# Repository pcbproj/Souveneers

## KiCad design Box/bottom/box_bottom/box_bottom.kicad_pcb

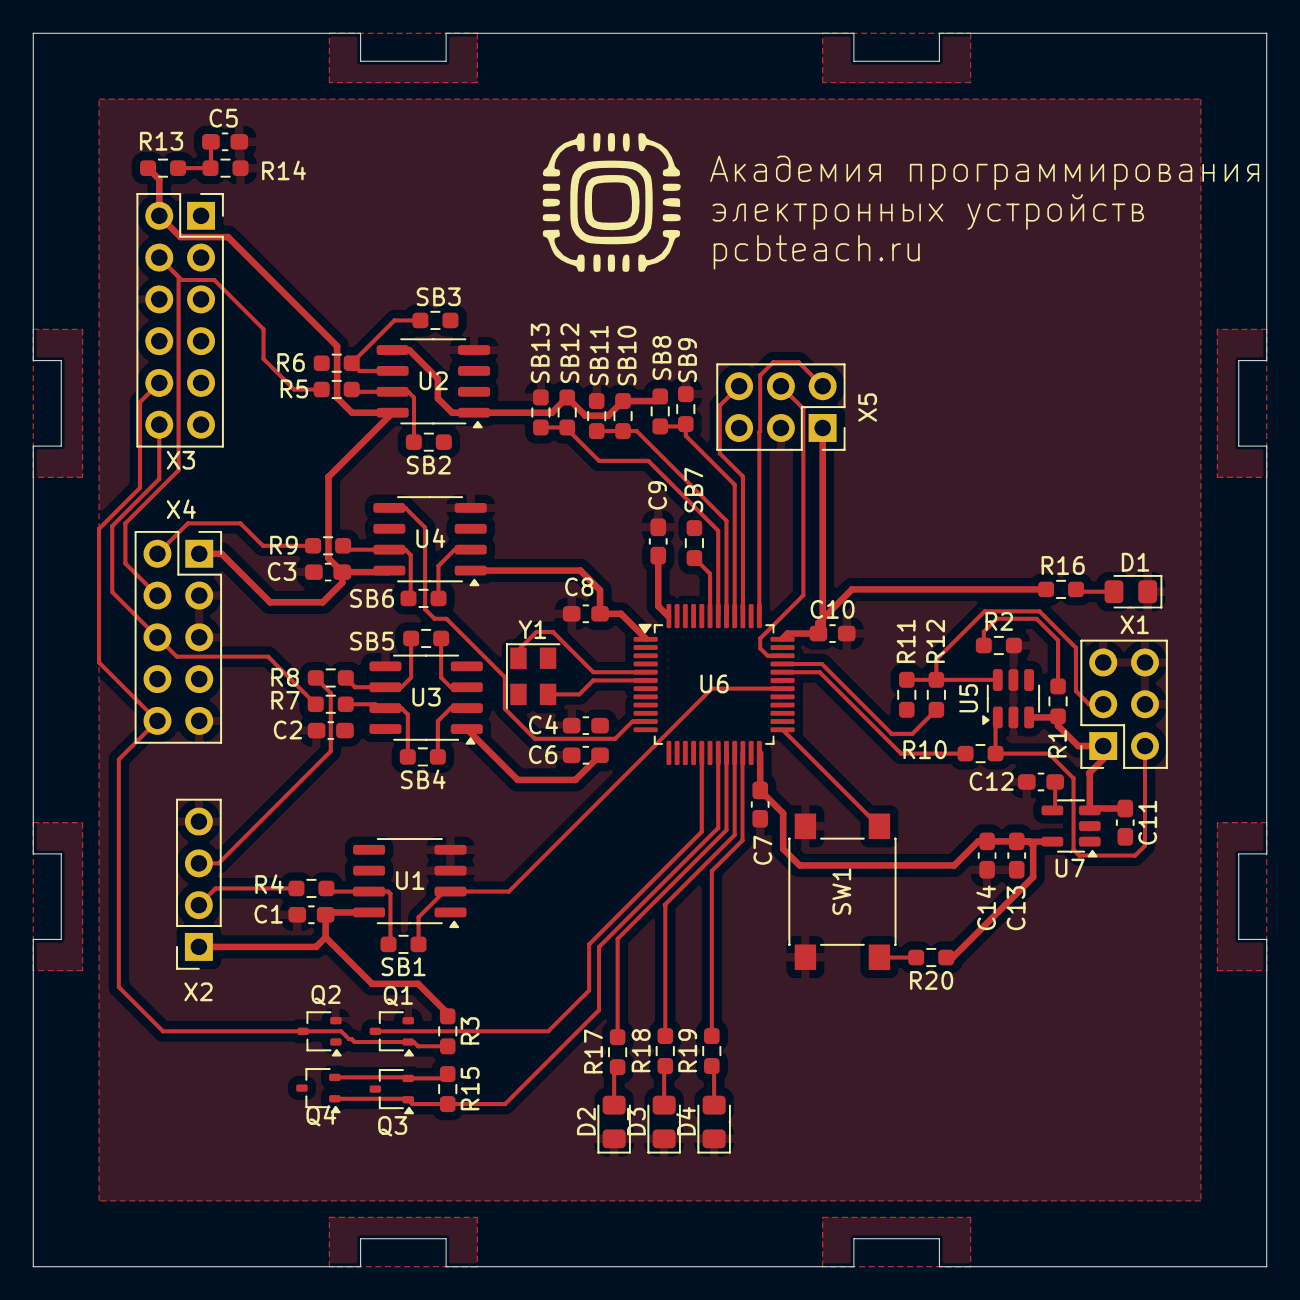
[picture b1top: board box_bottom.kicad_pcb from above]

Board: 2 copper layers, 75.0 x 75.0 mm, 69 parts (0 on the bottom side), 54 nets.

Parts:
C1, C2, C3, C4, C6, C7, C8, C9, C10, C14: 100n; C_0603_1608Metric_Pad1.08x0.95mm_HandSolder
C5: 1n; C_0603_1608Metric_Pad1.08x0.95mm_HandSolder
C11, C13: 1u; C_0603_1608Metric_Pad1.08x0.95mm_HandSolder
C12: 10n; C_0603_1608Metric_Pad1.08x0.95mm_HandSolder
D1, D2, D3, D4: LED; LED_0805_2012Metric_Pad1.15x1.40mm_HandSolder
Q1, Q2: 1N7002; SOT-323_SC-70
Q3, Q4: NTS4173; SOT-323_SC-70
R1, R13: 4k7; R_0603_1608Metric_Pad0.98x0.95mm_HandSolder
R2, R3, R14, R15, R20: 10k; R_0603_1608Metric_Pad0.98x0.95mm_HandSolder
R4, R5, R6, R7, R8, R9: 100; R_0603_1608Metric_Pad0.98x0.95mm_HandSolder
R10, R12: 22; R_0603_1608Metric_Pad0.98x0.95mm_HandSolder
R11: 1k5; R_0603_1608Metric_Pad0.98x0.95mm_HandSolder
R16: 330; R_0603_1608Metric_Pad0.98x0.95mm_HandSolder
R17, R18, R19: 470; R_0603_1608Metric_Pad0.98x0.95mm_HandSolder
SB1, SB2, SB3, SB4, SB5, SB6, SB7, SB8, SB9, SB10, SB11, SB12, SB13: JUMPER; R_0603_1608Metric_Pad0.98x0.95mm_HandSolder
SW1: BUTTON1; SW_SPST_PTS645
U1, U2, U3, U4: SN74LVC2T45; SOIC-8_3.9x4.9mm_P1.27mm
U5: ESDA5V3SC6; SOT-23-6
U6: STM32F103CBT6; LQFP-48_7x7mm_P0.5mm
U7: LP2985N; SOT-23-5
X1: Conn_01x06_Socket; PinSocket_2x03_P2.54mm_Vertical
X2: CONN-04P1L; PinSocket_1x04_P2.54mm_Vertical
X3: CONN-12P2L; PinSocket_2x06_P2.54mm_Vertical
X4: CONN-10P2L; PinSocket_2x05_P2.54mm_Vertical
X5: CONN-06P1L; PinSocket_2x03_P2.54mm_Vertical
Y1: 8MHz; Crystal_SMD_EuroQuartz_MT-4Pin_3.2x2.5mm

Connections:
+3V3BM: C6.1 (C1), C7.1 (C1), C8.1 (C1), C9.1 (C1), C10.1 (C1), C13.1 (C1), C14.1 (C1), Q3.3 (D), R16.2 (R2), R20.1 (R1), SB8.1 (J1), SB10.1 (J1), SB12.1 (J1), U1.1 (VCCA), U1.5 (DIR), U2.1 (VCCA), U2.5 (DIR), U3.1 (VCCA), U4.1 (VCCA), U6.1 (VBAT), U6.9 (VDDA), U6.24 (VDD), U6.36 (VDD), U6.48 (VDD), U7.5 (VO), X5.1
/5VUSB: C11.1 (C1), R1.1 (R1), U5.3 (IO2), U7.1 (VIN), U7.3 (ENA), X1.1
/BMBTN: R20.2 (R2), SW1.1 (CMN), U6.25 (PB12)
/JRST: C4.1 (C1), U6.7 (nRST), X5.5
/JSWCLK: U6.37 (PA14/SWCLK), X5.2
/JSWDIO: U6.34 (PA13/SWDIO), X5.4
/JSWO: U6.39 (JTDO/PB3), X5.6
/LED0: R17.2 (R2), U6.20 (PB2)
/LED1: R18.2 (R2), U6.21 (PB10)
/LED2: R19.2 (R2), U6.22 (PB11)
/PWR_BR: Q3.1 (G), Q4.1 (G), R15.1 (R1), U6.19 (PB1)
/TPWR: C5.1 (C1), R13.2 (R2), R14.1 (R1), U6.18 (PB0)
/UD+: R12.1 (R1), U6.33 (PA12)
/UD-: R10.2 (R2), U6.32 (PA11)
/VBUS: R1.2 (R2), R2.1 (R1), U6.26 (PB13)
/iRST: Q2.1 (G), U6.12 (PA2)
/iRST_SENSE: Q1.3 (D), U6.17 (PA7)
/iRXD: SB5.1 (J1), U3.3 (A2), U6.31 (PA10)
/iTCK: SB2.1 (J1), U2.2 (A1), U6.15 (PA5)
/iTDI: SB3.1 (J1), U2.3 (A2), U6.13 (PA3)
/iTDO: SB4.1 (J1), SB7.2 (J2), U3.2 (A1), U6.16 (PA6)
/iTMS: SB6.1 (J1), U4.2 (A1), U6.14 (PA4)
/iTMS_DIR: U4.5 (DIR), U6.11 (PA1)
/iTXD: SB1.1 (J1), U1.2 (A1), U6.30 (PA9)
/xPWR: C1.2 (C2), C2.2 (C2), C3.2 (C2), Q4.3 (D), R3.1 (R1), R13.1 (R1), U1.8 (VCCB), U2.8 (VCCB), U3.8 (VCCB), U4.8 (VCCB), X2.1, X3.2, X4.1
/xRST: Q1.1 (G), Q2.3 (D), R3.2 (R2), X3.10, X4.10
/xRXD: R8.1 (R1), X2.3
/xTCK: R5.1 (R1), X3.4, X4.4
/xTDI: R6.1 (R1), X4.8
/xTDO: R7.1 (R1), X3.12, X4.6
/xTMS: R9.1 (R1), X3.8, X4.2
/xTXD: R4.1 (R1), X2.2
unnamed: C12.1 (C1), U7.4 (BYP)
unnamed: D1.2 (A), R16.1 (R1)
unnamed: D2.2 (A), R17.1 (R1)
unnamed: D3.2 (A), R18.1 (R1)
unnamed: D4.2 (A), R19.1 (R1)
unnamed: Q3.2 (S), Q4.2 (S), R15.2 (R2)
unnamed: R4.2 (R2), SB1.2 (J2), U1.7 (B1)
unnamed: R5.2 (R2), SB2.2 (J2), U2.7 (B1)
unnamed: R6.2 (R2), SB3.2 (J2), U2.6 (B2)
unnamed: R7.2 (R2), SB4.2 (J2), U3.7 (B1)
unnamed: R8.2 (R2), SB5.2 (J2), U3.6 (B2)
unnamed: R9.2 (R2), SB6.2 (J2), U4.7 (B1)
unnamed: R10.1 (R1), U5.1 (IO1), X1.2
unnamed: R11.1 (R1), U6.29 (PA8)
unnamed: R11.2 (R2), R12.2 (R2), U5.6 (IO4), X1.3
unnamed: SB7.1 (J1), U6.43 (PB7)
unnamed: SB8.2 (J2), SB9.1 (J1), U6.40 (JRST/PB4)
unnamed: SB10.2 (J2), SB11.1 (J1), U6.41 (PB5)
unnamed: SB12.2 (J2), SB13.1 (J1), U6.42 (PB6)
unnamed: U6.5 (PD0/XI), Y1.1 (Q1)
unnamed: U6.6 (PD1/XO), Y1.3 (Q2)
PGND: C1.1 (C1), C2.1 (C1), C3.1 (C1), C4.2 (C2), C5.2 (C2), C6.2 (C2), C7.2 (C2), C8.2 (C2), C9.2 (C2), C10.2 (C2), C11.2 (C2), C12.2 (C2), C13.2 (C2), C14.2 (C2), D1.1 (K), D2.1 (K), D3.1 (K), D4.1 (K), Q1.2 (S), Q2.2 (S), R2.2 (R2), R14.2 (R2), SB9.2 (J2), SB11.2 (J2), SB13.2 (J2), SW1.2 (NO), U1.3 (A2), U1.4 (GND), U2.4 (GND), U3.4 (GND), U3.5 (DIR), U4.4 (GND), U5.2 (GND), U5.5 (GND), U6.8 (VSSA), U6.23 (VSS), U6.35 (VSS), U6.44 (PH3/BOOT0), U6.47 (VSS), U7.2 (GND), X1.4, X1.5, X1.6, X2.4, X3.5, X3.6, X4.3, X4.5, X4.9, X5.3, Y1.2 (CMN)

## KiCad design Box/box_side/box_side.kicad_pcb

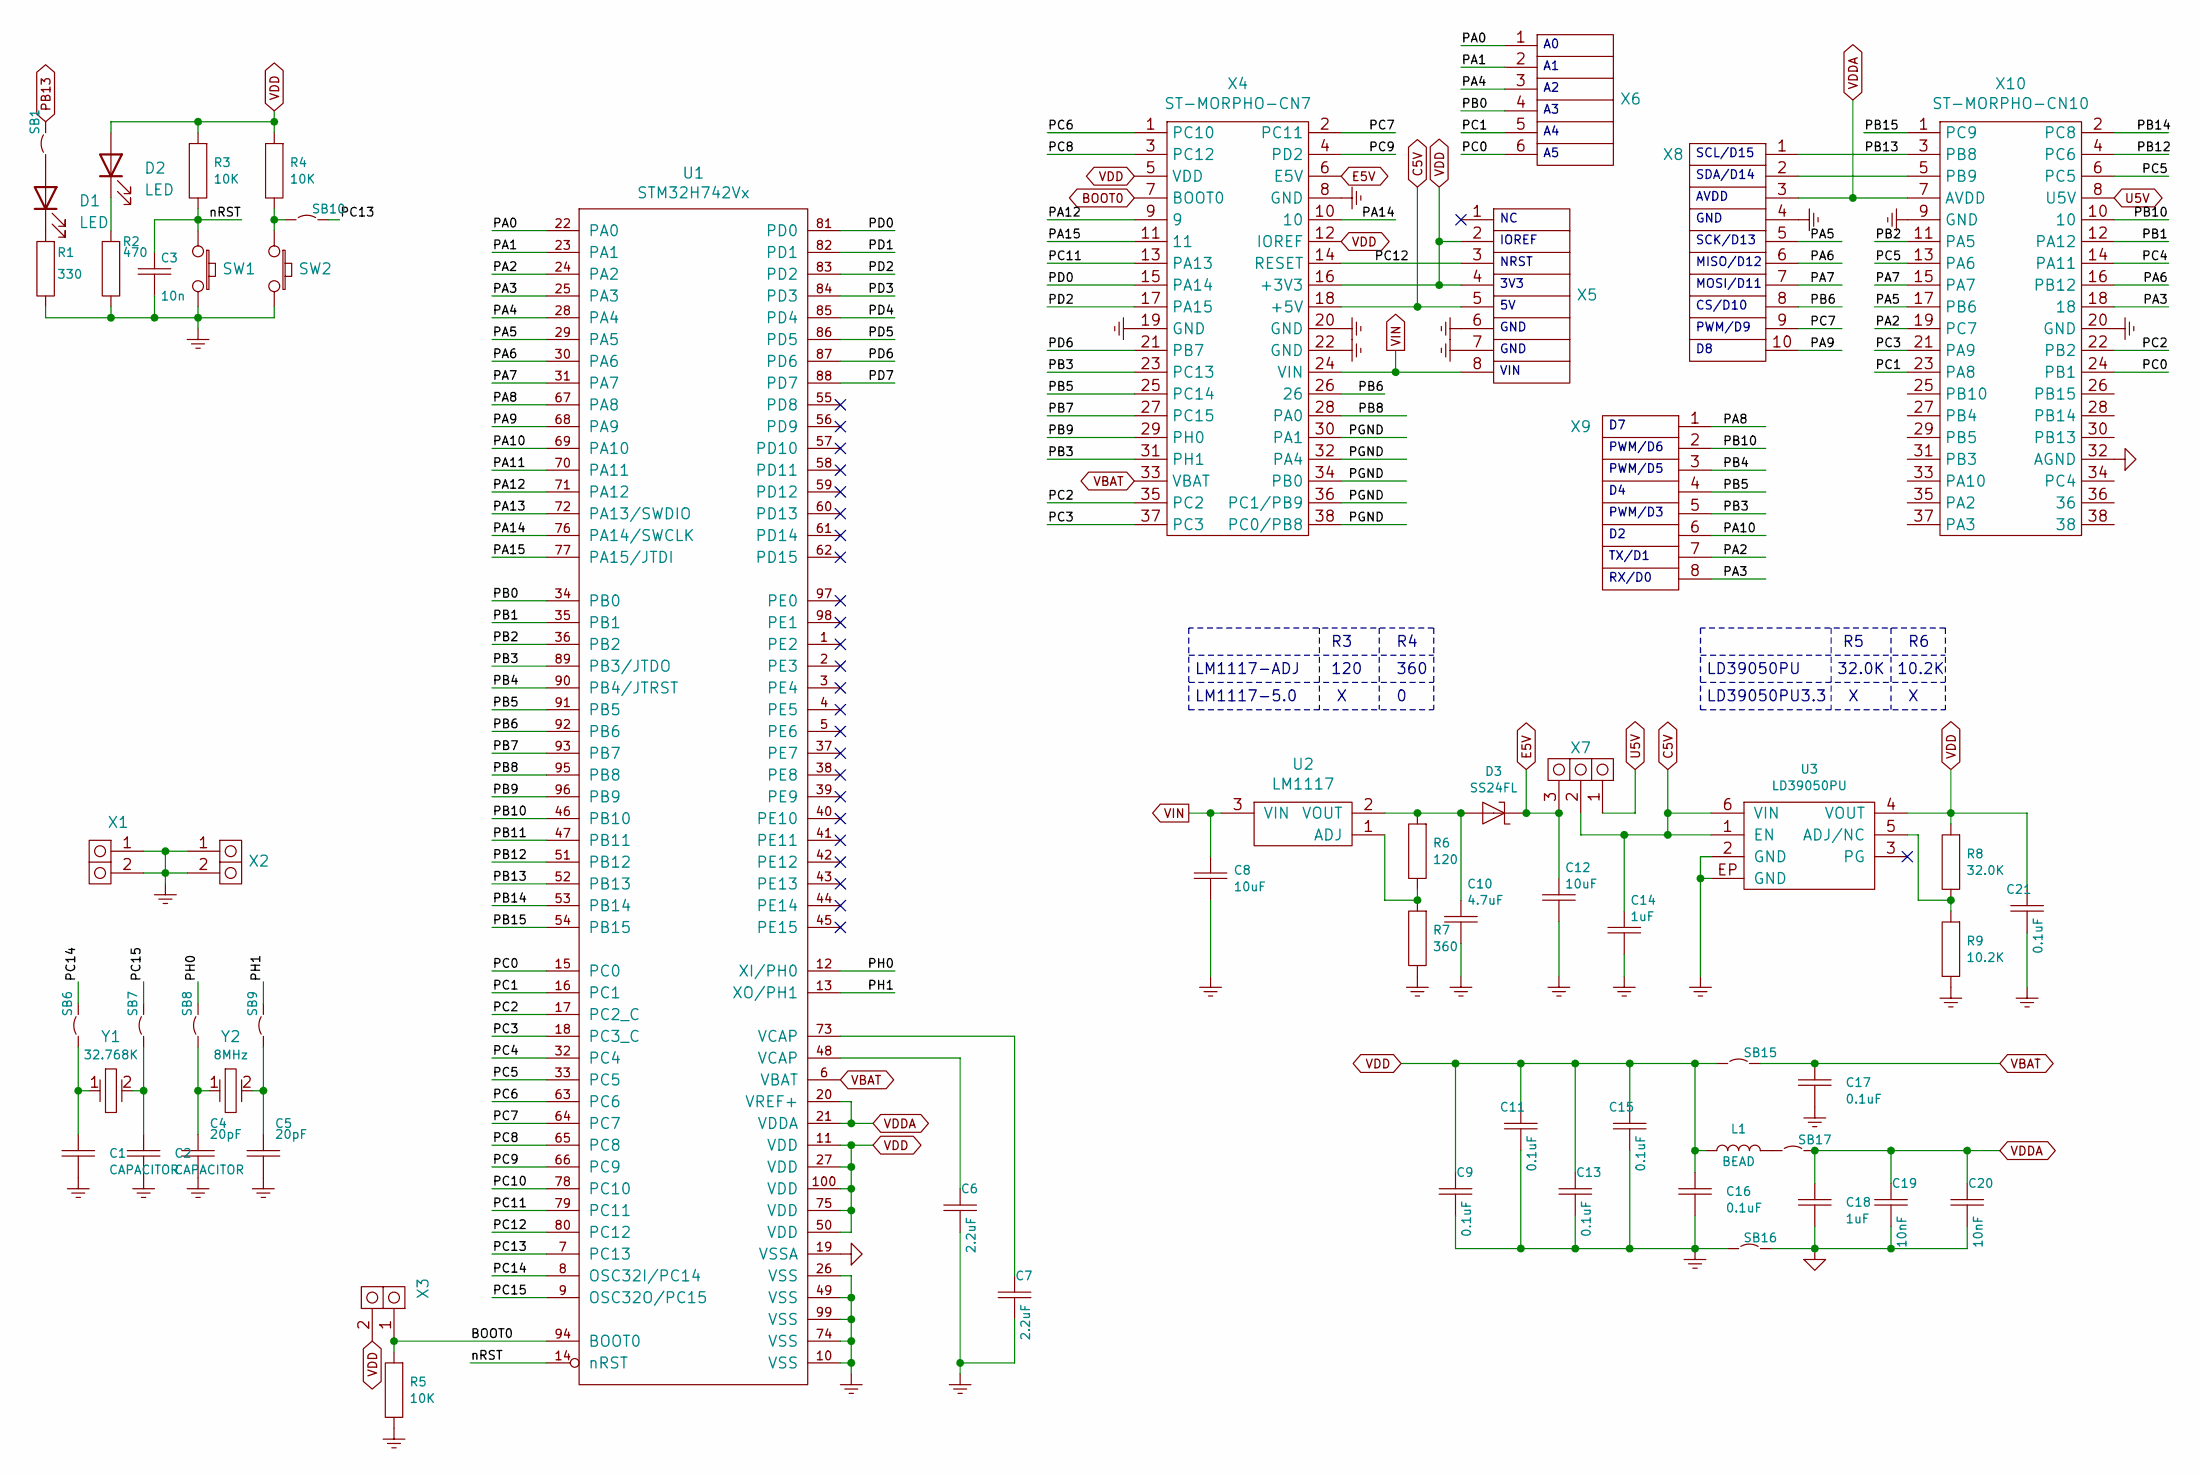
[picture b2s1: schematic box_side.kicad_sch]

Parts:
C1, C2: CAPACITOR; C_0603_1608Metric_Pad1.08x0.95mm_HandSolder
C3: 10n; C_0603_1608Metric_Pad1.08x0.95mm_HandSolder
C4, C5: 20pF; C_0603_1608Metric_Pad1.08x0.95mm_HandSolder
C6, C7: 2.2uF; C_0603_1608Metric_Pad1.08x0.95mm_HandSolder
C8, C12: 10uF; C_0805_2012Metric_Pad1.18x1.45mm_HandSolder
C9, C11, C13, C15, C16, C17, C21: 0.1uF; C_0603_1608Metric_Pad1.08x0.95mm_HandSolder
C10: 4.7uF; C_0603_1608Metric_Pad1.08x0.95mm_HandSolder
C14, C18: 1uF; C_0603_1608Metric_Pad1.08x0.95mm_HandSolder
C19, C20: 10nF; C_0603_1608Metric_Pad1.08x0.95mm_HandSolder
D1, D2: LED; LED_0805_2012Metric_Pad1.15x1.40mm_HandSolder
D3: SS24FL; D_SOD-123F
L1: BEAD; L_0805_2012Metric_Pad1.05x1.20mm_HandSolder
R1: 330; R_0603_1608Metric_Pad0.98x0.95mm_HandSolder
R2: 470; R_0603_1608Metric_Pad0.98x0.95mm_HandSolder
R3, R4, R5: 10K; R_0603_1608Metric_Pad0.98x0.95mm_HandSolder
R6: 120; R_0603_1608Metric_Pad0.98x0.95mm_HandSolder
R7: 360; R_0603_1608Metric_Pad0.98x0.95mm_HandSolder
R8: 32.0K; R_0603_1608Metric_Pad0.98x0.95mm_HandSolder
R9: 10.2K; R_0603_1608Metric_Pad0.98x0.95mm_HandSolder
SB1, SB6, SB7, SB8, SB9, SB10, SB15, SB16, SB17: JUMPER; R_0603_1608Metric_Pad0.98x0.95mm_HandSolder
SW1, SW2: BUTTON1; SW_SPST_PTS645
U1: STM32H742Vx; LQFP-100_14x14mm_P0.5mm
U2: LM1117; SOT-223
U3: LD39050PU; DFN-6-1EP_2x1.8mm_P0.5mm_EP1.2x1.6mm
X1, X2: CONN-02P1LA; PinSocket_1x02_P2.54mm_Vertical
X3: CONN-02P1L; PinSocket_1x02_P2.54mm_Vertical
X4: ST-MORPHO-CN7; PinSocket_2x19_P1.27mm_Vertical_SMD
X5, X9: CONN-08P1L; PinSocket_1x08_P2.54mm_Vertical
X6: CONN-06P1L; PinSocket_1x06_P2.54mm_Vertical
X7: CONN-03P1L; PinSocket_1x03_P2.54mm_Vertical
X8: CONN-10P1L; PinSocket_2x05_P2.54mm_Vertical
X10: ST-MORPHO-CN10; PinSocket_2x19_P1.27mm_Vertical_SMD
Y1: 32.768K; Crystal_SMD_EuroQuartz_EQ161-2Pin_3.2x1.5mm_HandSoldering
Y2: 8MHz; Crystal_SMD_5032-2Pin_5.0x3.2mm

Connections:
/PA0: U1.22 (PA0), X6.1
/PA1: U1.23 (PA1), X6.2
/PA2: U1.24 (PA2), X9.7, X10.19 (PC7)
/PA3: U1.25 (PA3), X9.8, X10.18
/PA4: U1.28 (PA4), X6.3
/PA5: U1.29 (PA5), X8.5, X10.17 (PB6)
/PA6: U1.30 (PA6), X8.6, X10.16 (PB12)
/PA7: U1.31 (PA7), X8.7, X10.15 (PA7)
/PA8: U1.67 (PA8), X9.1
/PA9: U1.68 (PA9), X8.10
/PA10: U1.69 (PA10), X9.6
/PA11: U1.70 (PA11)
/PA12: U1.71 (PA12), X4.9
/PA13: U1.72 (PA13/SWDIO)
/PA14: U1.76 (PA14/SWCLK), X4.10
/PA15: U1.77 (PA15/JTDI), X4.11
/PB0: U1.34 (PB0), X6.4
/PB1: U1.35 (PB1), X10.12 (PA12)
/PB2: U1.36 (PB2), X10.11 (PA5)
/PB3: U1.89 (PB3/JTDO), X4.23 (PC13), X4.31 (PH1), X9.5
/PB4: U1.90 (PB4/JTRST), X9.3
/PB5: U1.91 (PB5), X4.25 (PC14), X9.4
/PB6: U1.92 (PB6), X4.26, X8.8
/PB7: U1.93 (PB7), X4.27 (PC15)
/PB8: U1.95 (PB8), X4.28 (PA0)
/PB9: U1.96 (PB9), X4.29 (PH0)
/PB10: U1.46 (PB10), X9.2, X10.10
/PB11: U1.47 (PB11)
/PB12: U1.51 (PB12), X10.4 (PC6)
/PB14: U1.53 (PB14), X10.2 (PC8)
/PB15: U1.54 (PB15), X10.1 (PC9)
/PC0: U1.15 (PC0), X6.6, X10.24 (PB1)
/PC1: U1.16 (PC1), X6.5, X10.23 (PA8)
/PC2: U1.17 (PC2_C), X4.35 (PC2), X10.22 (PB2)
/PC3: U1.18 (PC3_C), X4.37 (PC3), X10.21 (PA9)
/PC4: U1.32 (PC4), X10.14 (PA11)
/PC5: U1.33 (PC5), X10.6 (PC5), X10.13 (PA6)
/PC6: U1.63 (PC6), X4.1 (PC10)
/PC7: U1.64 (PC7), X4.2 (PC11), X8.9
/PC8: U1.65 (PC8), X4.3 (PC12)
/PC9: U1.66 (PC9), X4.4 (PD2)
/PC10: U1.78 (PC10)
/PC11: U1.79 (PC11), X4.13 (PA13)
/PC12: U1.80 (PC12), X4.14 (RESET), X5.3
/PC13: SB10.2 (J2), U1.7 (PC13)
/PC14: SB6.2 (J2), U1.8 (OSC32I/PC14); also elsewhere on the board
/PC15: SB7.2 (J2), U1.9 (OSC32O/PC15); also elsewhere on the board
/PD0: U1.81 (PD0), X4.15 (PA14)
/PD1: U1.82 (PD1)
/PD2: U1.83 (PD2), X4.17 (PA15)
/PD3: U1.84 (PD3)
/PD4: U1.85 (PD4)
/PD5: U1.86 (PD5)
/PD6: U1.87 (PD6), X4.21 (PB7)
/PD7: U1.88 (PD7)
/PH0: SB8.2 (J2), U1.12 (XI/PH0); also elsewhere on the board
/PH1: SB9.2 (J2), U1.13 (XO/PH1); also elsewhere on the board
/nRST: C3.1 (C1), R3.2 (R2), SW1.1 (CMN), U1.14 (nRST)
AGND: C18.2 (C2), C19.2 (C2), C20.2 (C2), SB16.2 (J2), U1.19 (VSSA), X10.32 (AGND)
BOOT0: R5.1 (R1), U1.94 (BOOT0), X3.1, X4.7 (BOOT0)
C5V: C14.1 (C1), U3.1 (EN), U3.6 (VIN), X4.18 (+5V), X5.5, X7.2
E5V: C12.1 (C1), D3.1 (K), X4.6 (E5V), X7.3
unnamed: C1.1 (C1), SB6.1 (J1), Y1.1 (Q1)
unnamed: C2.1 (C1), SB7.1 (J1), Y1.2 (Q2)
unnamed: C4.1 (C1), SB8.1 (J1), Y2.1 (Q1)
unnamed: C5.1 (C1), SB9.1 (J1), Y2.2 (Q2)
unnamed: C6.1 (C1), U1.48 (VCAP)
unnamed: C7.1 (C1), U1.73 (VCAP)
unnamed: C10.1 (C1), D3.2 (A), R6.1 (R1), U2.2 (VOUT)
unnamed: D1.2 (A), SB1.1 (J1)
unnamed: D1.1 (K), R1.1 (R1)
unnamed: D2.1 (K), R2.1 (R1)
unnamed: L1.2 (R2), SB17.1 (J1)
unnamed: R4.2 (R2), SB10.1 (J1), SW2.1 (CMN)
unnamed: R6.2 (R2), R7.1 (R1), U2.1 (ADJ)
unnamed: R8.2 (R2), R9.1 (R1), U3.5 (ADJ/NC)
unnamed: X8.2, X10.5 (PB9)
PB13: SB1.2 (J2), U1.52 (PB13), X8.1, X10.3 (PB8)
PGND: C1.2 (C2), C2.2 (C2), C3.2 (C2), C4.2 (C2), C5.2 (C2), C6.2 (C2), C7.2 (C2), C8.2 (C2), C9.2 (C2), C10.2 (C2), C11.2 (C2), C12.2 (C2), C13.2 (C2), C14.2 (C2), C15.2 (C2), C16.2 (C2), C17.2 (C2), C21.2 (C2), R1.2 (R2), R2.2 (R2), R5.2 (R2), R7.2 (R2), R9.2 (R2), SB16.1 (J1), SW1.2 (NO), SW2.2 (NO), U1.10 (VSS), U1.26 (VSS), U1.49 (VSS), U1.74 (VSS), U1.99 (VSS), U3.2 (GND), U3.EP (GND), X1.1, X1.2, X2.1, X2.2, X4.8 (GND), X4.19 (GND), X4.20 (GND), X4.22 (GND), X4.30 (PA1), X4.32 (PA4), X4.34 (PB0), X4.36 (PC1/PB9), X4.38 (PC0/PB8), X5.6, X5.7, X8.4, X10.9 (GND), X10.20 (GND)
U5V: X7.1, X10.8 (U5V)
VBAT: C17.1 (C1), SB15.2 (J2), U1.6 (VBAT), X4.33 (VBAT)
VDD: C9.1 (C1), C11.1 (C1), C13.1 (C1), C15.1 (C1), C16.1 (C1), C21.1 (C1), D2.2 (A), L1.1 (R1), R3.1 (R1), R4.1 (R1), R8.1 (R1), SB15.1 (J1), U1.11 (VDD), U1.27 (VDD), U1.50 (VDD), U1.75 (VDD), U1.100 (VDD), U3.4 (VOUT), X3.2, X4.5 (VDD), X4.12 (IOREF), X4.16 (+3V3), X5.2, X5.4
VDDA: C18.1 (C1), C19.1 (C1), C20.1 (C1), SB17.2 (J2), U1.20 (VREF+), U1.21 (VDDA), X8.3, X10.7 (AVDD)
VIN: C8.1 (C1), U2.3 (VIN), X4.24 (VIN), X5.8

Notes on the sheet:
120
10.2K
GND
PWM/D9
RX/D0
SCL/D15
MOSI/D11
3V3
AVDD
PWM/D3
TX/D1
VIN
SCK/D13
32.0K
IOREF
LM1117-ADJ
PWM/D6
LM1117-5.0
LD39050PU3.3
CS/D10
360
NRST
LD39050PU
SDA/D14
PWM/D5
MISO/D12

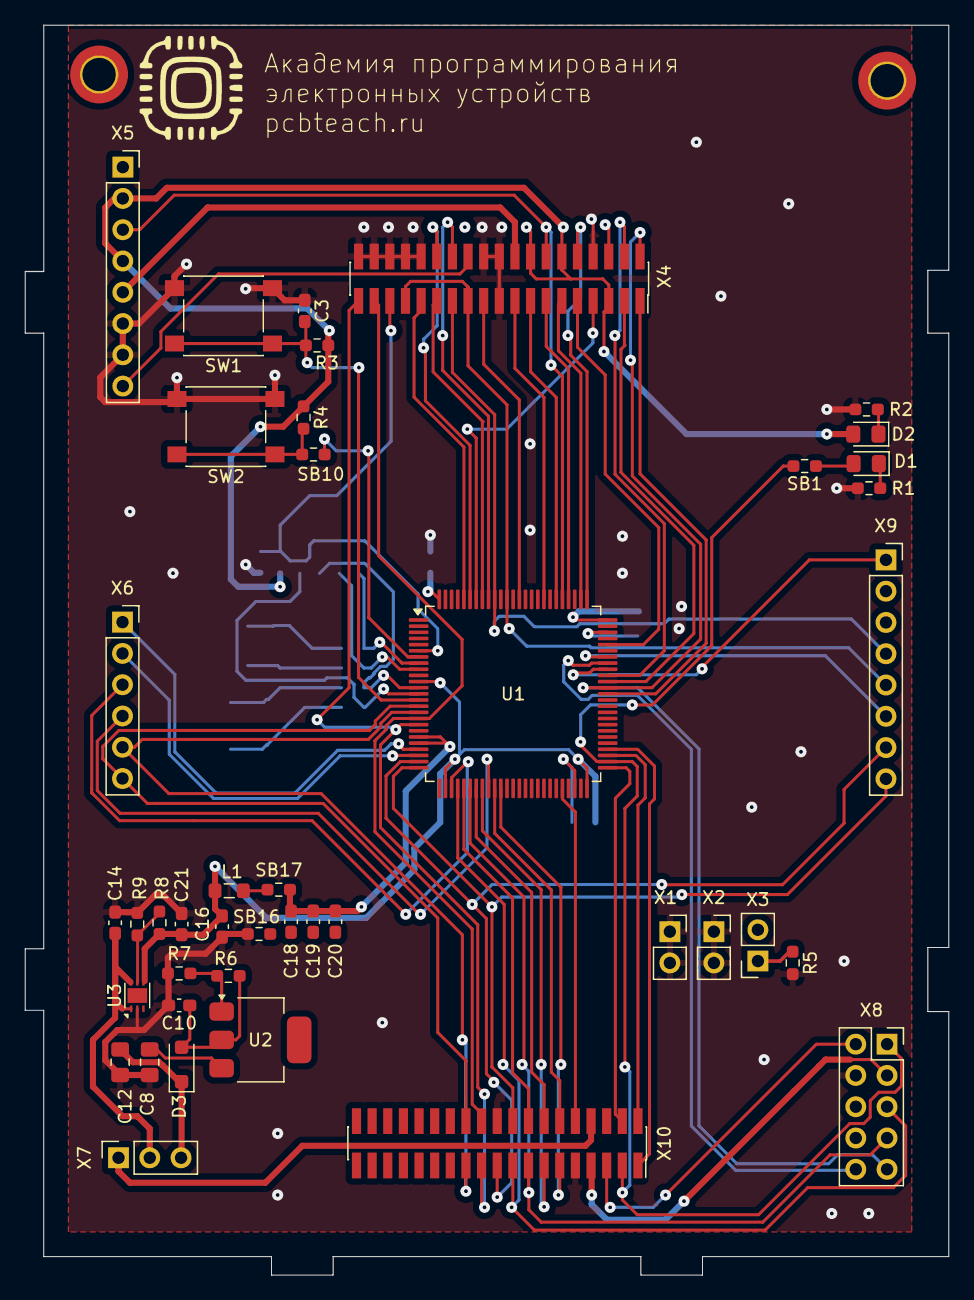
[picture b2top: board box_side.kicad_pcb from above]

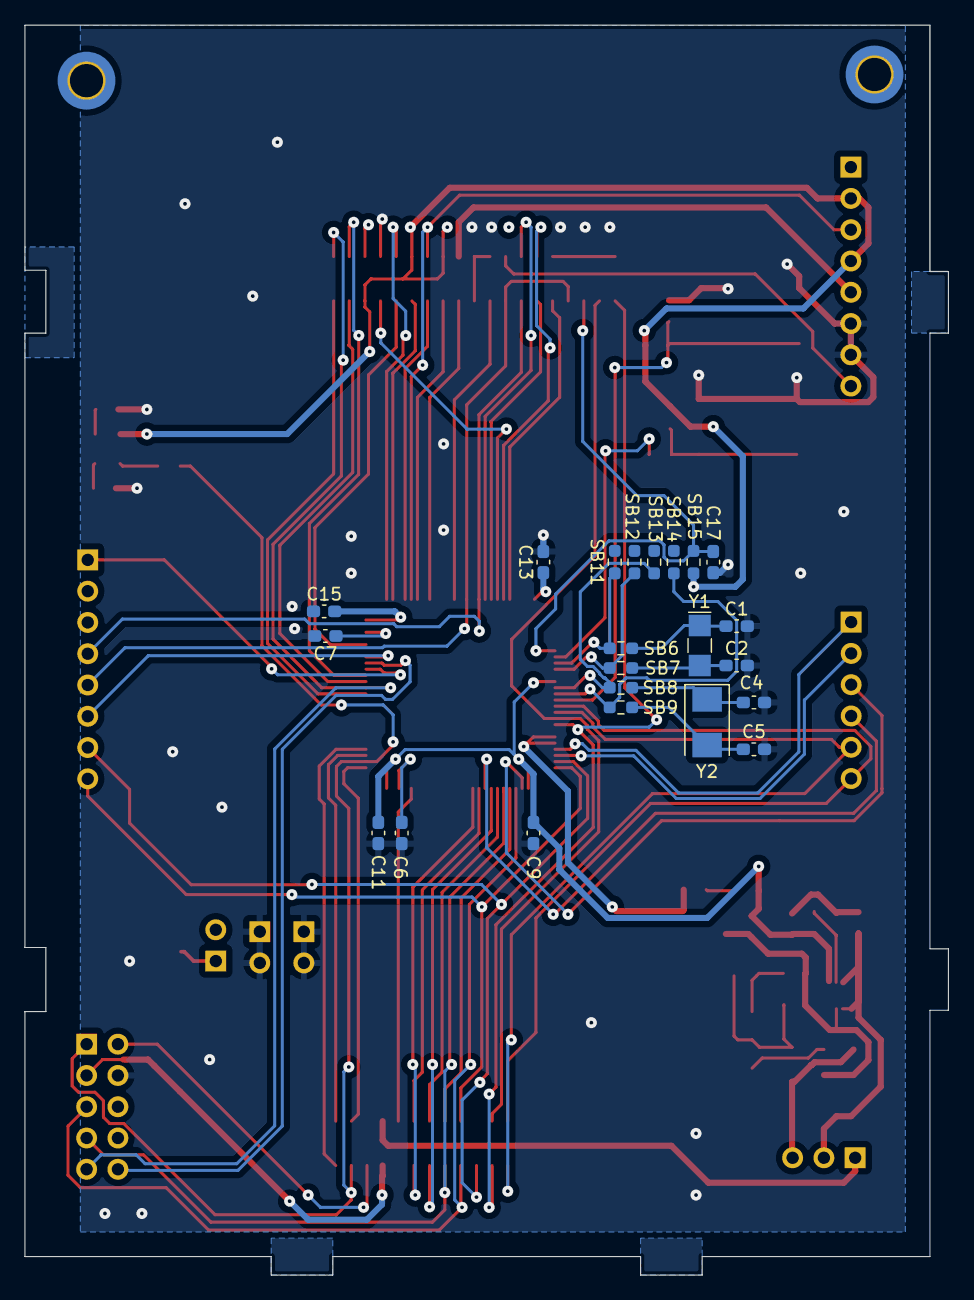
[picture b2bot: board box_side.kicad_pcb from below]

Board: 2 copper layers, 75.0 x 101.5 mm, 64 parts (22 on the bottom side), 75 nets.

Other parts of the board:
SB11, SB12, SB13, SB14: JUMPER; R_0603_1608Metric_Pad0.98x0.95mm_HandSolder

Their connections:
/PC14: SB11.1 (J1); also elsewhere on the board
/PC15: SB12.1 (J1); also elsewhere on the board
/PH0: SB13.1 (J1); also elsewhere on the board
/PH1: SB14.1 (J1); also elsewhere on the board

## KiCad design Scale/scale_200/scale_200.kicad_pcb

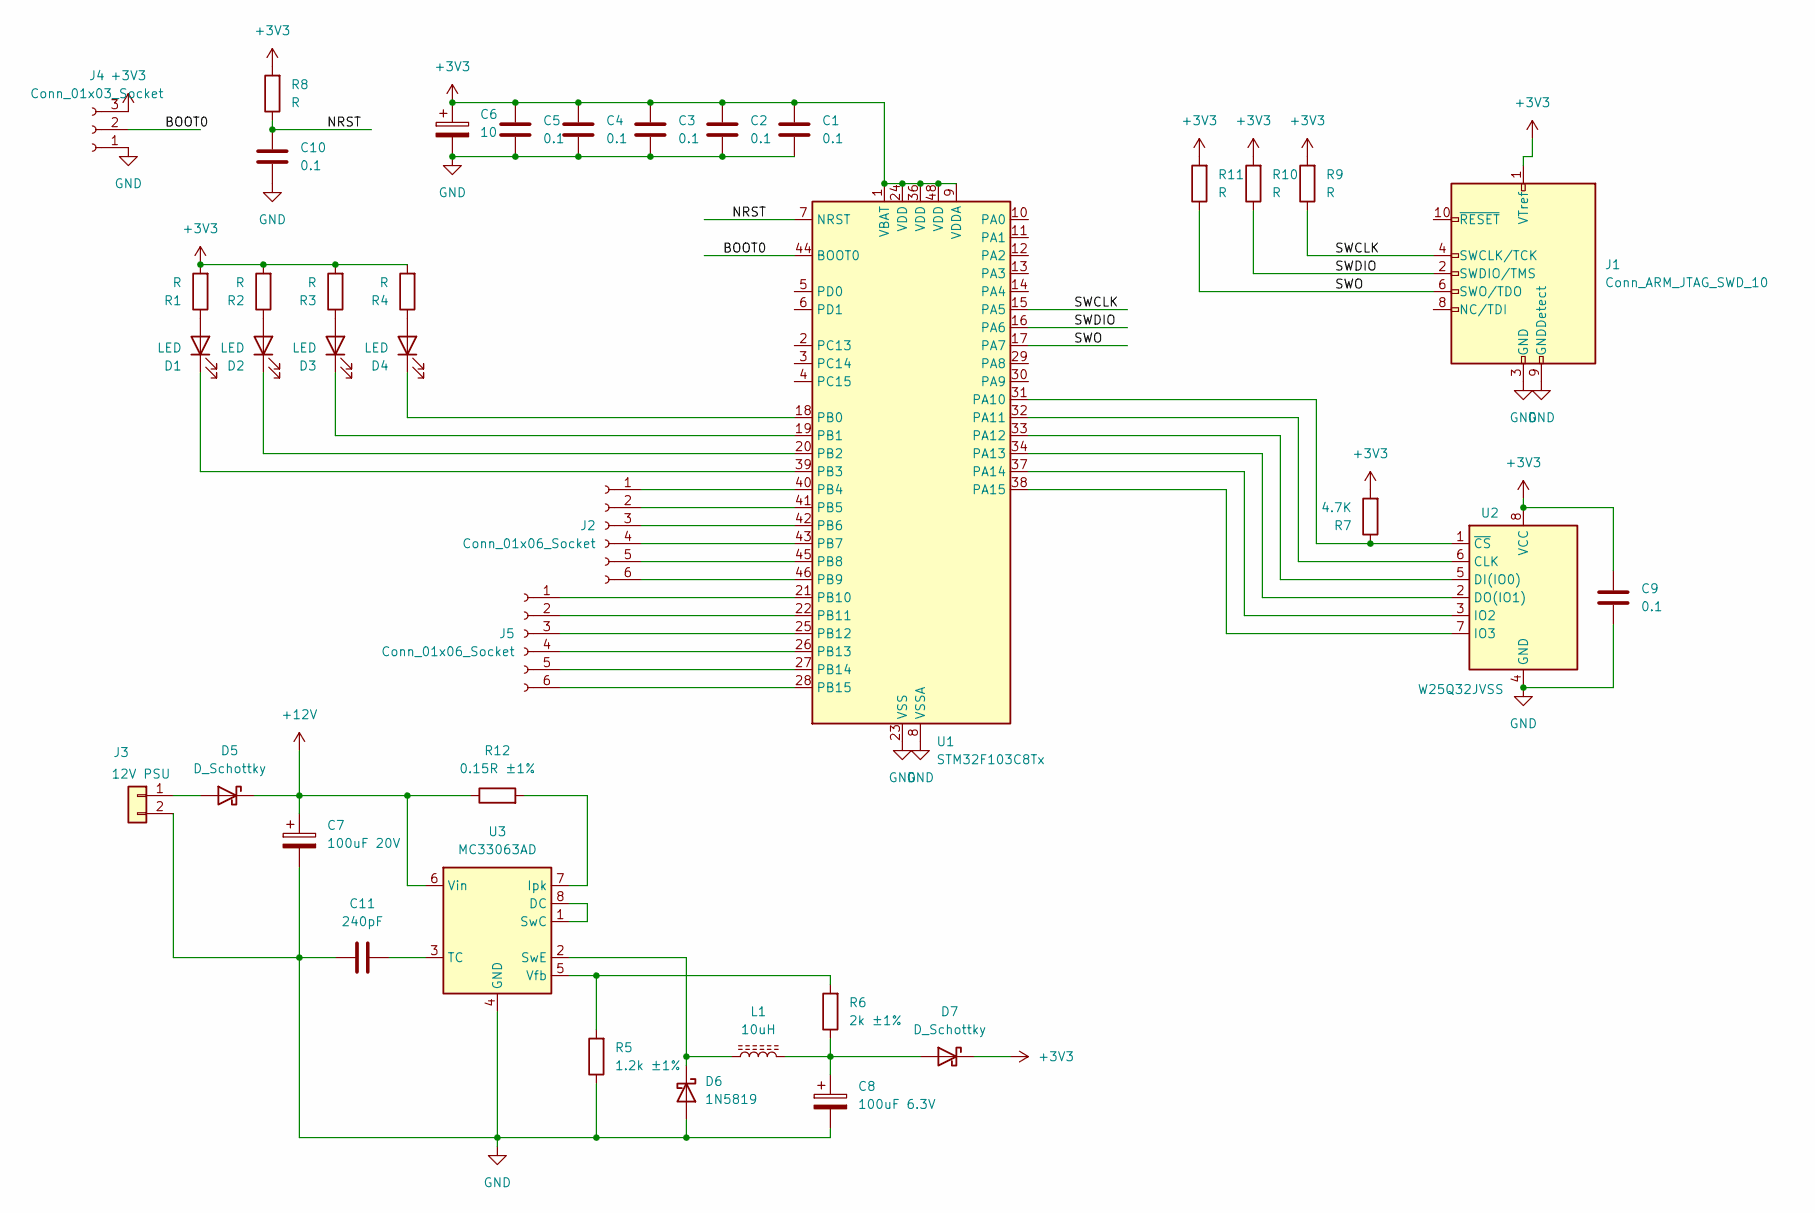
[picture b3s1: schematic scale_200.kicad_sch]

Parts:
C1, C2, C3, C4, C5, C9, C10: 0.1; C_0603_1608Metric
C6: 10; CP_Elec_5x3.9
C7: 100uF 20V; CP_Elec_5x3.9
C8: 100uF 6.3V; CP_Elec_5x3.9
C11: 240pF; C_0603_1608Metric
D1, D2, D3, D4: LED; LED_1206_3216Metric
D5, D7: D_Schottky; D_SOD-123
D6: 1N5819; D_SOD-123
J1: Conn_ARM_JTAG_SWD_10; PinSocket_2x05_P2.54mm_Vertical
J2, J5: Conn_01x06_Socket; PinSocket_1x06_P2.54mm_Vertical
J3: 12V PSU; PinSocket_1x02_P2.54mm_Vertical
J4: Conn_01x03_Socket; PinSocket_1x03_P2.54mm_Vertical
L1: 10uH; L_TDK_SLF6028
R1, R2, R3, R4, R8, R9, R10, R11: R; R_0805_2012Metric_Pad1.20x1.40mm_HandSolder
R5: 1.2k ±1%; R_0805_2012Metric_Pad1.20x1.40mm_HandSolder
R6: 2k ±1%; R_0805_2012Metric_Pad1.20x1.40mm_HandSolder
R7: 4.7K; R_0805_2012Metric_Pad1.20x1.40mm_HandSolder
R12: 0.15R ±1%; R_2512_6332Metric_Pad1.40x3.35mm_HandSolder
U1: STM32F103C8Tx; LQFP-48_7x7mm_P0.5mm
U2: W25Q32JVSS; SOIC-8_5.23x5.23mm_P1.27mm
U3: MC33063AD; SOIC-8_3.9x4.9mm_P1.27mm

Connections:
+3V3: C1.1, C2.1, C3.1, C4.1, C5.1, C6.1, C9.1, D7.1 (K), J1.1 (VTref), J4.3, R1.2, R2.2, R3.2, R4.2, R7.2, R8.2, R9.2, R10.2, R11.2, U1.1 (VBAT), U1.9 (VDDA), U1.24 (VDD), U1.36 (VDD), U1.48 (VDD), U2.8 (VCC)
+12V: C7.1, D5.1 (K), R12.1, U3.6 (Vin)
/BOOT0: J4.2, U1.44 (BOOT0)
/NRST: C10.1, R8.1, U1.7 (NRST)
/SWCLK: J1.4 (SWCLK/TCK), R9.1, U1.15 (PA5)
/SWDIO: J1.2 (SWDIO/TMS), R10.1, U1.16 (PA6)
/SWO: J1.6 (SWO/TDO), R11.1, U1.17 (PA7)
GND: C1.2, C2.2, C3.2, C4.2, C5.2, C6.2, C7.2, C8.2, C9.2, C10.2, C11.1, D6.2 (A), J1.3 (GND), J1.5 (GND), J1.9 (GNDDetect), J3.2, J4.1, R5.1, U1.8 (VSSA), U1.23 (VSS), U1.35 (VSS), U1.47 (VSS), U2.4 (GND), U3.4 (GND)
unnamed: D1.2 (A), R1.1
unnamed: D1.1 (K), U1.39 (PB3)
unnamed: D2.2 (A), R2.1
unnamed: D2.1 (K), U1.20 (PB2)
unnamed: D3.2 (A), R3.1
unnamed: D3.1 (K), U1.19 (PB1)
unnamed: D4.2 (A), R4.1
unnamed: D4.1 (K), U1.18 (PB0)
unnamed: D5.2 (A), J3.1
unnamed: D6.1 (K), L1.1, U3.2 (SwE)
unnamed: C8.1, D7.2 (A), L1.2, R6.1
unnamed: J2.1, U1.40 (PB4)
unnamed: J2.2, U1.41 (PB5)
unnamed: J2.3, U1.42 (PB6)
unnamed: J2.4, U1.43 (PB7)
unnamed: J2.5, U1.45 (PB8)
unnamed: J2.6, U1.46 (PB9)
unnamed: J5.1, U1.21 (PB10)
unnamed: J5.2, U1.22 (PB11)
unnamed: J5.3, U1.25 (PB12)
unnamed: J5.4, U1.26 (PB13)
unnamed: J5.5, U1.27 (PB14)
unnamed: J5.6, U1.28 (PB15)
unnamed: R7.1, U1.31 (PA10), U2.1 (~CS)
unnamed: U1.32 (PA11), U2.6 (CLK)
unnamed: U1.33 (PA12), U2.5 (DI(IO0))
unnamed: U1.34 (PA13), U2.2 (DO(IO1))
unnamed: U1.37 (PA14), U2.3 (IO2)
unnamed: U1.38 (PA15), U2.7 (IO3)
unnamed: U3.1 (SwC), U3.8 (DC)
unnamed: R12.2, U3.7 (Ipk)
unnamed: C11.2, U3.3 (TC)
unnamed: R5.2, R6.2, U3.5 (Vfb)

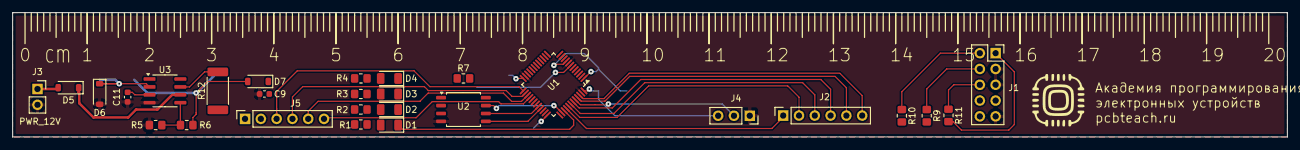
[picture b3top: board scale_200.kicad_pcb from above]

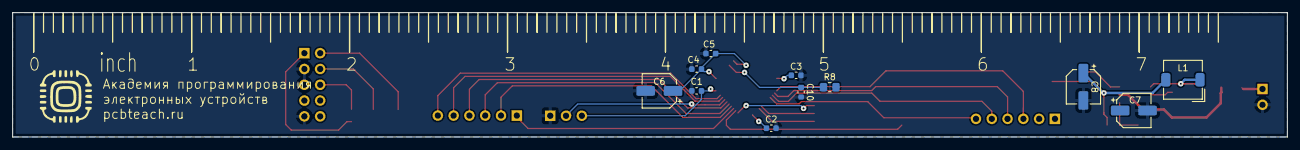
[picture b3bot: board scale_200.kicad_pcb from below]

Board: 2 copper layers, 205.0 x 20.0 mm, 39 parts (11 on the bottom side), 41 nets.

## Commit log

2024-11-16 first commit, local repository
2024-11-16 scale allmost ready. Logo need to add and contacts
2024-11-16 backups removed
2024-11-17 scale done. Just GERBER left
2024-11-17 box bottom done. gerber generated OK
2024-11-20 some edits
2024-11-20 all gerbers done
